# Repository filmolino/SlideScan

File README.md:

# SlideScan

**Note:** There is a new version of the slide scanner using a M5Stack Fire for more info visit [Filmolino SlideScanner](https://github.com/filmolino/SlideScanner)

Filmolino SlideScan is a device that makes it easy to scan slides in magazines fully automatic using a modified slide projector and a digital camera. It controls the slide projector and a digital camera using a cable release or an infrared remote control (Nikon, Canon, Pentax, Sony, Olympus, Minolta). It is powered directly from the slide projector or over a mini USB connector. New cable releases and IR controls can easy be added to the software. 
 
Thanks to the [M5StampC3 from M5Stack](https://shop.m5stack.com/collections/m5-controllers/products/m5stamp-c3-mate-with-pin-headers) using a [ESP32-C3 RISC-V microcontroller from Espressif](https://www.espressif.com/en/products/socs/esp32-c3) it is also possible to control the SlideScan through a web interface over WiFi. The scanner has it's own access point to which you can connect.

Everything of the SlideScan is open source, so you can easy build your own!

## Guide
### Camera connection
You can connect your digital camera using a cable connection or infrared remote control. To control your camera using the cable release you need a shutter release cable for your camera with a 2.5 mm jack connector on the other end. You can find the right cable for your camera searching the web for *JJC Remote Control Shutter Release Cable*. They are not expensive you should get one for about 10 EUR.

### DIN cable connection to pcb
Connect the male 6 pin DIN connector as follows to the PCB J2:

| Pin DIN | Pin PCB |Function |
| --- | --- | --- |
| 1 | 4 | Reverse slide transport |
| 2 | 3 | Forward slide transport |
| 3 | 2 | Positive DC voltage |
| 4 | x | Not used |
| 5 | x | Not used |
| 6 | 1 | Negative DC voltage (only needed if you want to power SlideScan from the projector) |

### Slide projector connection
**Important: Use the Tape/remote control socket and not the lap dissolve socket.**
Connect the 6 pin DIN connector of the Filmolino SlideScan to the *remote control socket* of your slide projector. SlideScan can be powered from the slide projector or you can power it over the Mini USB connector. 

To power it from the projector the following components *R2, C4, U1, C3, D2* need to be assembled on the pcb. If you power SlideScan over USB you don't need this components.

To not damage your SlideScan or slide projector check the pin map below first!
| 6 pin DIN connector | Function |
| --- | --- |
| 1 | Reverse slide transport |
| 2 | Forward slide transport |
| 3 | Positive DC voltage **max. 42 VDC!** (This voltage is usually about 30...35 VDC on most slide projectors) |
| 4 | Focus motor |
| 5 | Not used |
| 6 | Negative DC voltage |

### USB power
If you don't want to power your SlideScan from the slide projector connect an USB charger to the mini USB connector of the SlideScan.

### Turn on
Now you are ready to turn SlideScan on. To do so turn on the slide projector and if needed the USB charger.
After turning on the green LED should light up and the red one slowly blinking (because there is no WiFi connection yet).

### WiFi Connection
SlideScan starts its own WiFi access point: 

Default WiFi credentials
| ID | value |
| --- | --- |
| SSID | scanner |
| Password | filmolino |
| IP | 192.168.4.1 |

To see the web user interface do the following:
1. Connect your PC/Tablet/... to the SlideScan network with the SSID **scanner** using the password **filmolino**
2. In your webbrowser enter the address: **192.168.4.1**
3. Now you should see the web interface of the scanner

### Configuration
To see the configuration menu click on **Config**.

#### Access Point
Here you can change the SSID and the password.

#### WiFi Network
Not implemented yet.

#### Scanning
Here you can config the SlideScan.

##### Slide Change Time
This is the time the slide projector needs to change the slide.
Unit is milliseconds (1 second = 1000 milliseconds)

##### Slide Change Pulse Time
Duration of the pulse for the slide transport. During this time the slide transport contacts are closed. 
Unit is milliseconds (1 second = 1000 milliseconds)

##### Scan Time
This is the time the digital camera needs to capture (scan) the slide
Unit is milliseconds (1 second = 1000 milliseconds)

##### Slides to scan
Number of slides in the magazine.

##### Selected cable release
Can be OFF or the cable release you want to use.

##### Selected Infrared Release Code
Can be OFF or the brand name of your digital camera.

##### Buttons
| Button | Function |
| --- | --- |
| Save | Saves the changes |
| Delete Config | Deletes the actual configuration, you need to click the *Restart System* button after that |
| Restart System | Restarts the scanner |

### Standalone operation 
The device is controlled with only two buttons. The functions are as follows:

| Button | Short press | Long press |
| --- | --- | --- |
| Left | Forward slide transport | Backward slide transport |
| Right | Trigger camera (if auto an auto scan is active, stop it) | Start auto scan |

The actual state is indicated by a bi-color LED:
| State | LED green | LED red |
| --- | --- | --- |
| Running and no WiFi connection | ON | BLINK slowly |
| Running with WiFi connection | ON | OFF |
| Auto scan active | BLINK | OFF |
| Error | OFF | ON |

#### Auto Scan
When starting an Auto Scan the scan is always starts with image 1 and then the number of images is scanned. If the image counter is higher it will be reset to 1 before start.

### WiFi operation
Connect to the WiFi and open the address **192.168.4.1** in your webbrowser as described above. The SlideScan is connected as long as you see the green connected sign in the top left corner.

This view shows the current slide counter and the slides in the magazine (0/50). 
You can start an auto scan or manually scan slides using the five buttons below. If you want to change the current configuration click *Config* in the top right corner.

Buttons
| Button 1 | Button 2 | Button 3 | Button 4 | Button 5 |
| --- | --- | --- | --- | --- |
| Start Auto Scan | Forward | Backward | Capture (Scan) | Reset current slide |

To change to number of slides in the current magazine you can click on the current slide counter or go to the config menu.

## Hardware
You can find the KiCAD project with complete schematic and pcb design in the hardware folder. The double sided pcb can be easily soldered by hand. It uses just a few SMD components in not too small cases (0805). The components are easily available from the usual distributors.

## Software
### Project
The software is build with ESP-IDF using platform.io and Visual Studio Code.

## Documentation
The documentation with images can be found in the docs folder.

## To do
- slidescan.local address not working yet. So you have to point your browser to the default IP **192.168.4.1**
- Station mode (to connect to a WiFi network) not working yet
- Tested with Nikon and Pentax cameras

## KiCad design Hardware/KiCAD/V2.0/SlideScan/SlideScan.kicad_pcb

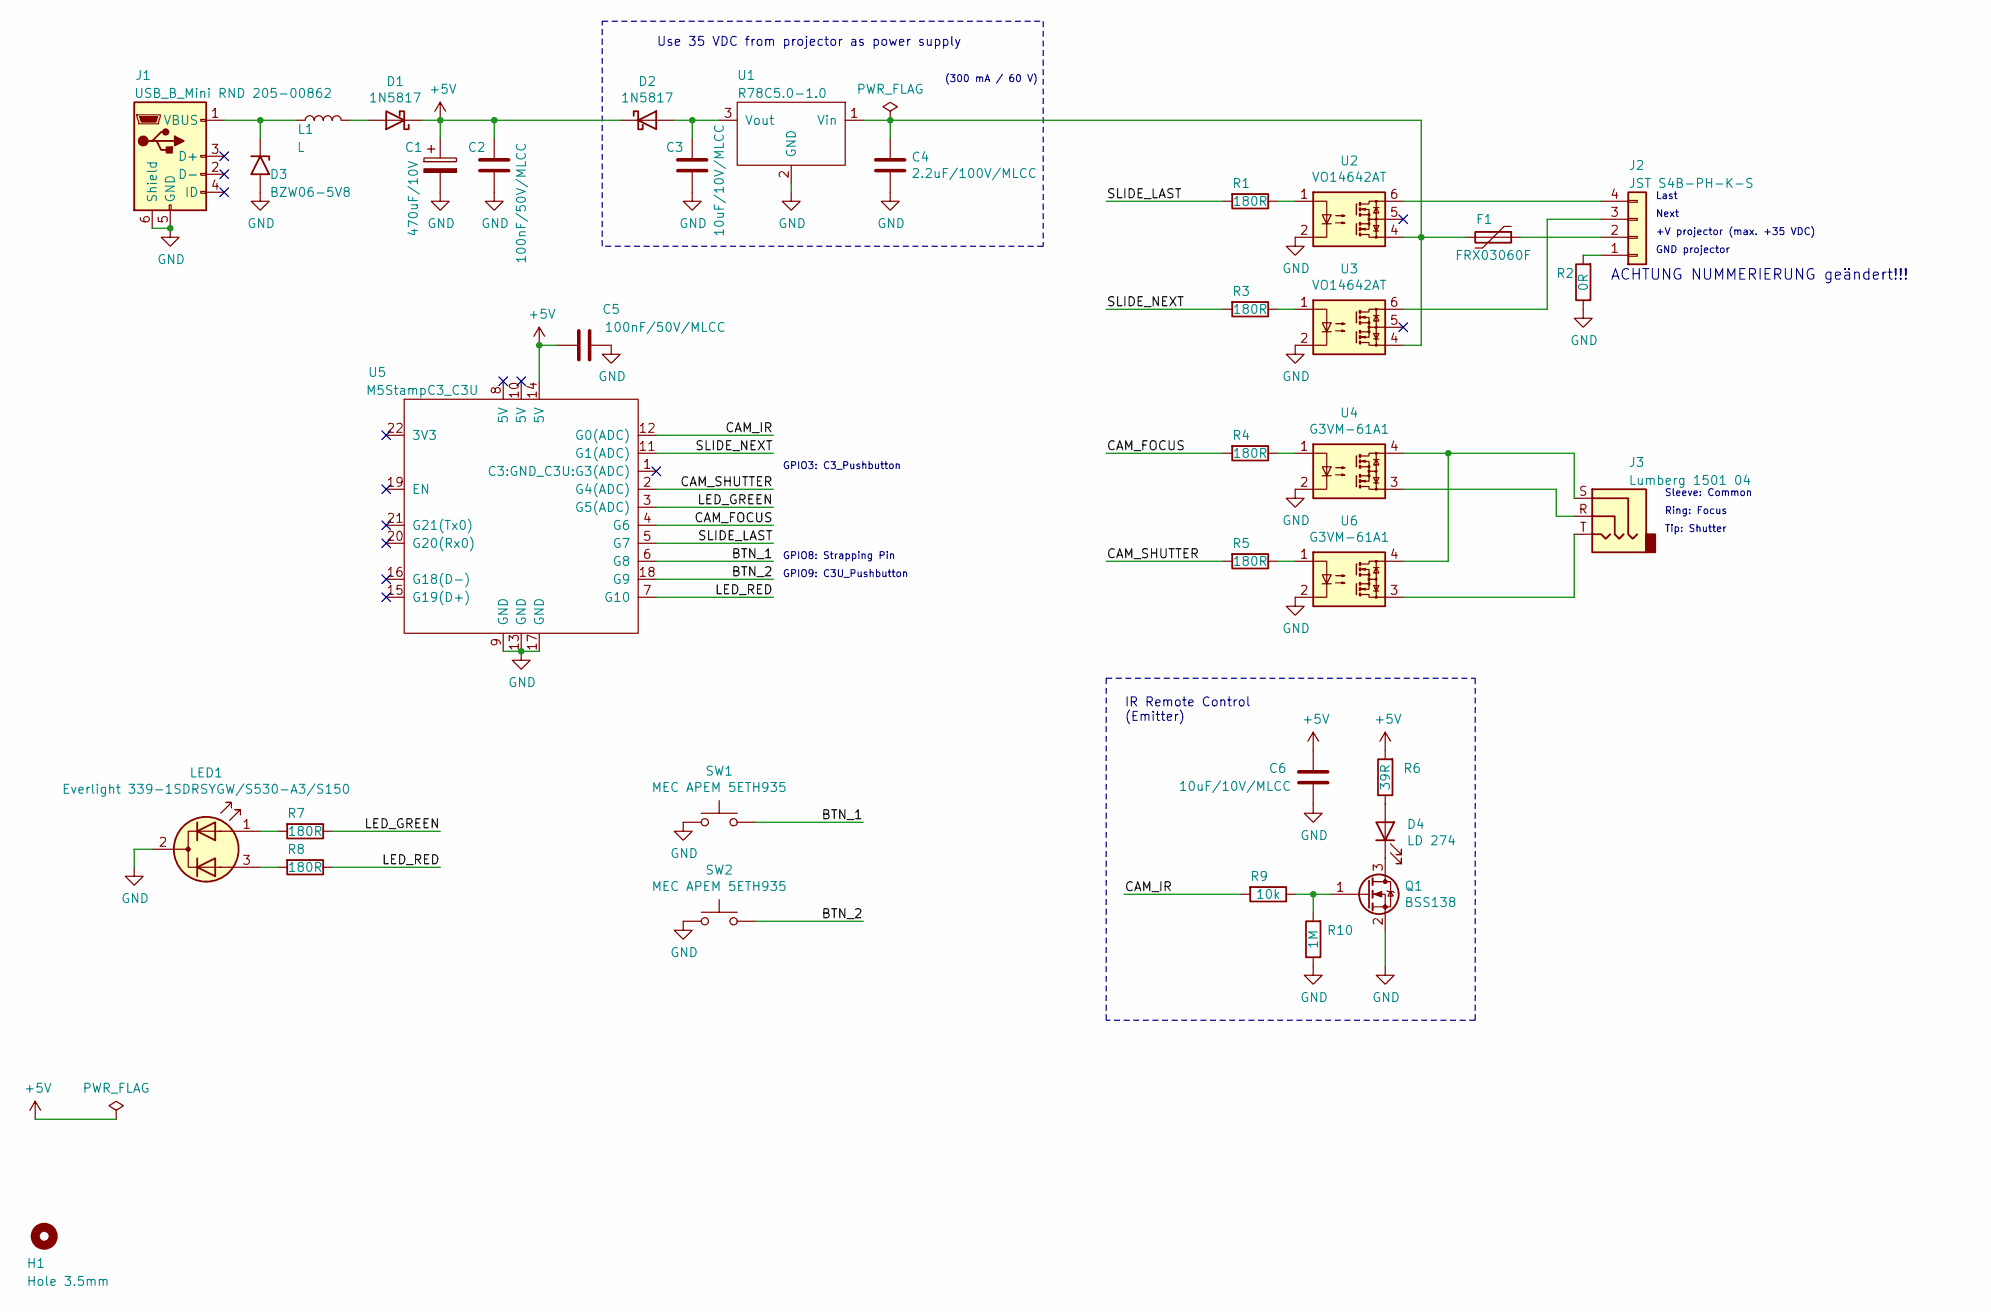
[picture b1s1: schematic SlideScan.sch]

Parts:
C1: 470uF/10V; CP_Radial_D8.0mm_P3.50mm
C2, C5: 100nF/50V/MLCC; C_0805_2012Metric_Pad1.18x1.45mm_HandSolder
C3, C6: 10uF/10V/MLCC; C_0805_2012Metric_Pad1.18x1.45mm_HandSolder
C4: 2.2uF/100V/MLCC; C_1210_3225Metric_Pad1.33x2.70mm_HandSolder
D1, D2: 1N5817; D_DO-41_SOD81_P10.16mm_Horizontal
D3: BZW06-5V8; D_DO-15_P10.16mm_Horizontal
D4: LD 274; LED_D5.0mm_Horizontal_O1.27mm_Z3.0mm_IRBlack
F1: FRX03060F; RV_Disc_D9mm_W3.3mm_P5mm
H1: Hole 3.5mm; MountingHole_3.5mm
J1: USB_B_Mini RND 205-00862; USB_Mini_RND_205-00862
J2: JST S4B-PH-K-S; JST_S4B-PH-K-S(LF)(SN)
J3: Lumberg 1501 04; Jack_2.5mm_Lumberg_1501_04
L1: L; L_0805_2012Metric_Pad1.15x1.40mm_HandSolder
LED1: Everlight 339-1SDRSYGW/S530-A3/S150; LED_D5.0mm-3_Everlight
Q1: BSS138; SOT-23
R1, R3, R4, R5, R7, R8: 180R; R_0805_2012Metric_Pad1.20x1.40mm_HandSolder
R2: 0R; R_0805_2012Metric_Pad1.20x1.40mm_HandSolder
R6: 39R; R_0805_2012Metric_Pad1.20x1.40mm_HandSolder
R9: 10k; R_0805_2012Metric_Pad1.20x1.40mm_HandSolder
R10: 1M; R_0805_2012Metric_Pad1.20x1.40mm_HandSolder
SW1, SW2: MEC APEM 5ETH935; SW_MEC_5ETH9
U1: R78C5.0-1.0; RECOM_SIP3_R-78C5.0-1.0
U2, U3: VO14642AT; DIP-6_W7.62mm_LongPads
U4, U6: G3VM-61A1; DIP-4_W7.62mm_LongPads
U5: M5StampC3_C3U; M5StampC3

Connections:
+5V: C1.1, C2.1, C5.2, C6.1, D1.1 (K), D2.1 (K), R6.2, U5.14 (5V)
/BTN_1: SW1.2, U5.6 (G8)
/BTN_2: SW2.2, U5.18 (G9)
/CAM_FOCUS: R4.2, U5.4 (G6)
/CAM_IR: R9.2, U5.12 (G0(ADC))
/CAM_SHUTTER: R5.2, U5.2 (G4(ADC))
/LED_GREEN: R7.1, U5.3 (G5(ADC))
/LED_RED: R8.1, U5.7 (G10)
/SLIDE_LAST: R1.2, U5.5 (G7)
/SLIDE_NEXT: R3.2, U5.11 (G1(ADC))
GND: C1.2, C2.2, C3.2, C4.2, C5.1, C6.2, D3.2 (A2), J1.5 (GND), J1.6 (Shield), LED1.2 (K), Q1.2 (S), R2.1, R10.1, SW1.1, SW2.1, U1.2 (GND), U2.2, U3.2, U4.2, U5.9 (GND), U5.13 (GND), U5.17 (GND), U6.2
unnamed: C3.1, D2.2 (A), U1.3 (Vout)
unnamed: C4.1, F1.2, U1.1 (Vin), U2.4, U3.4
unnamed: D1.2 (A), L1.2
unnamed: D3.1 (A1), J1.1 (VBUS), L1.1
unnamed: D4.1 (K), Q1.3 (D)
unnamed: D4.2 (A), R6.1
unnamed: F1.1, J2.2
unnamed: J2.1, R2.2
unnamed: J2.3, U3.6
unnamed: J2.4, U2.6
unnamed: J3.R, U4.3
unnamed: J3.S, U4.4, U6.4
unnamed: J3.T, U6.3
unnamed: LED1.1 (A1), R7.2
unnamed: LED1.3 (A2), R8.2
unnamed: Q1.1 (G), R9.1, R10.2
unnamed: R1.1, U2.1
unnamed: R3.1, U3.1
unnamed: R4.1, U4.1
unnamed: R5.1, U6.1

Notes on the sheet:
Use 35 VDC from projector as power supply
GPIO3: C3_Pushbutton
GPIO9: C3U_Pushbutton
(300 mA / 60 V)
Last
Next
+V projector (max. +35 VDC)
GND projector
Sleeve: Common
Ring: Focus
Tip: Shutter
IR Remote Control (Emitter)
GPIO8: Strapping Pin
ACHTUNG NUMMERIERUNG geändert!!!

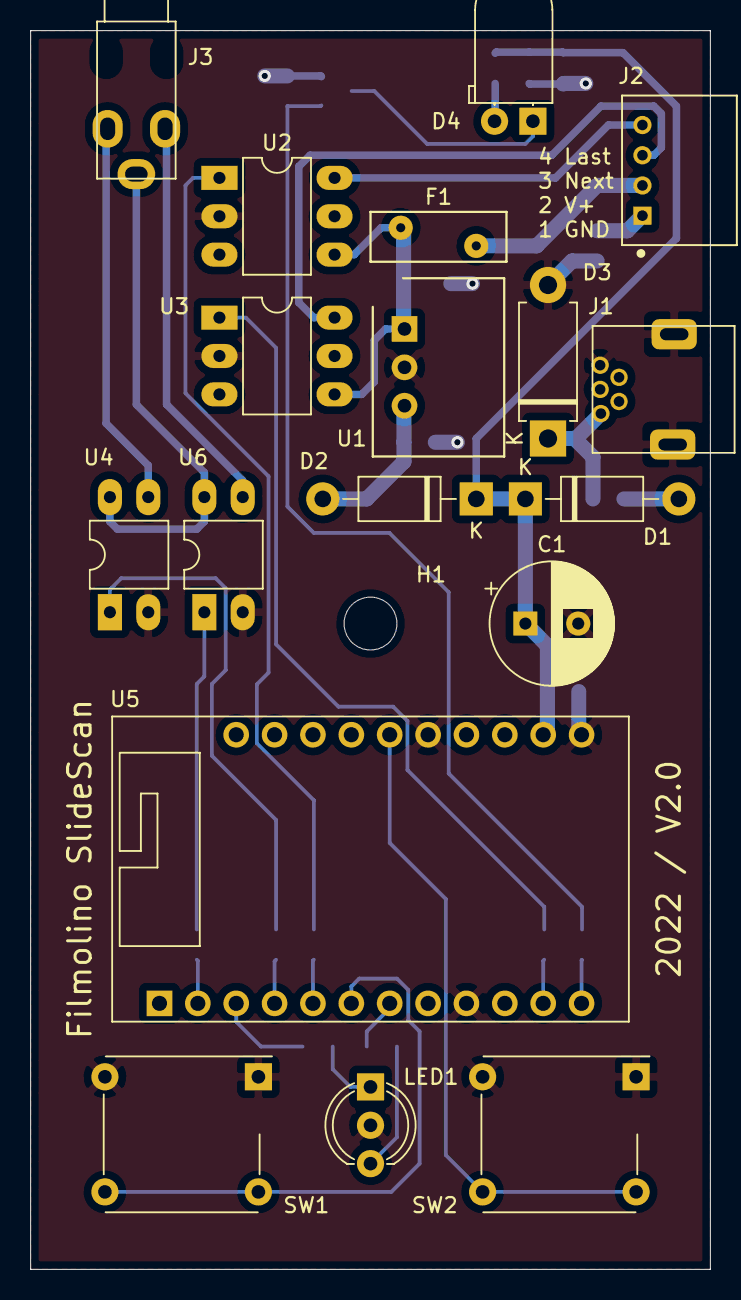
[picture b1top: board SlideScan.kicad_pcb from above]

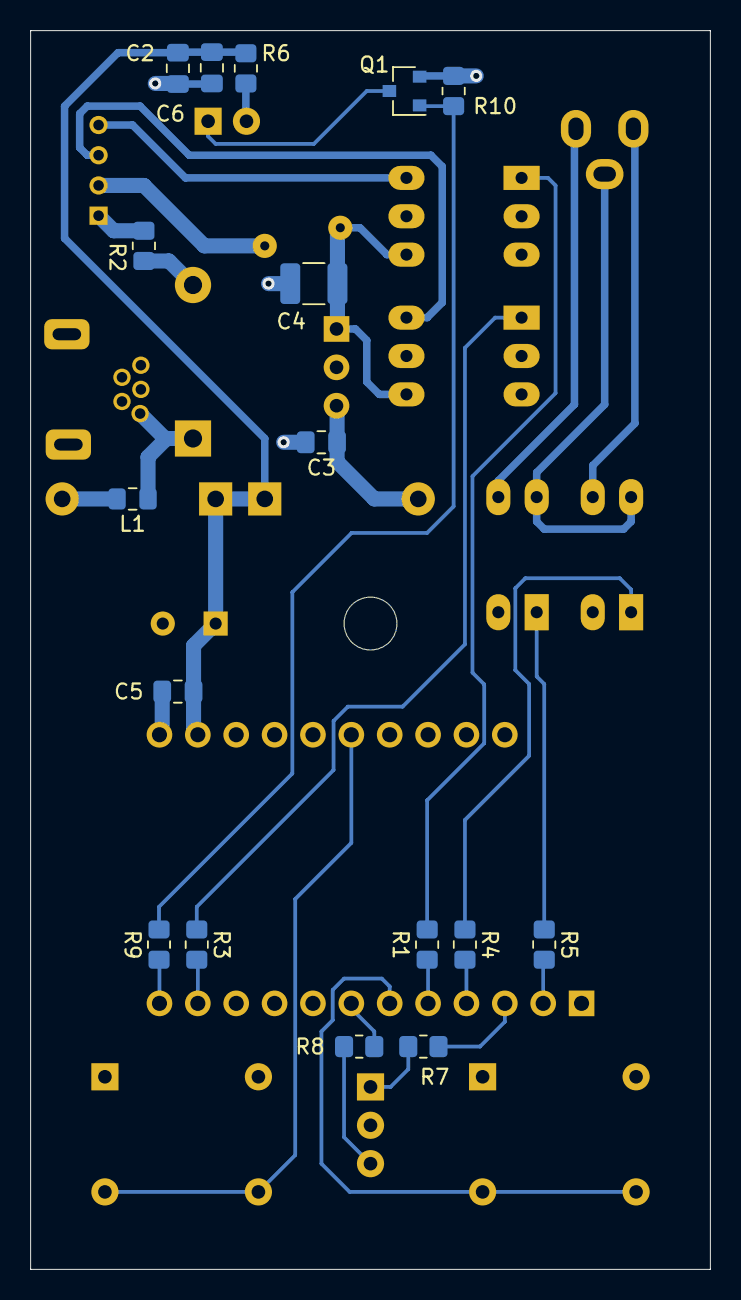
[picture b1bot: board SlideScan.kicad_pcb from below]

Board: 2 copper layers, 45.0 x 82.0 mm, 36 parts (17 on the bottom side), 31 nets.

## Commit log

2022-06-24 Publish to web
